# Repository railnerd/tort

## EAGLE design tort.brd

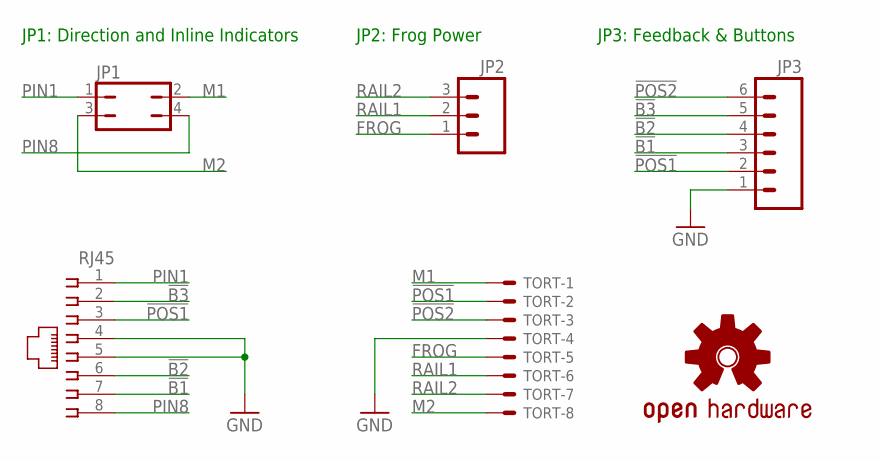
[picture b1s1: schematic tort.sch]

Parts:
JP1: JP2Q
JP2: M03-SCREW-5MM; SCREWTERMINAL-5MM-3
JP3: M063.5MM-6; SCREWTERMINAL-3.5MM-6
LOGO1: OSHW-LOGOL; OSHW-LOGO-L
RJ45: 215877-7
STANDOFF1: STAND-OFF
TORT: KK-156-8

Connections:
!B1: JP3.3, RJ45.7
!B2: JP3.4, RJ45.6
!B3: JP3.5, RJ45.2
!POS1: JP3.2, RJ45.3, TORT.2
!POS2: JP3.6, TORT.3
FROG: JP2.1, TORT.5
GND: JP3.1, RJ45.4, RJ45.5, TORT.4
M1: JP1.2, TORT.1
M2: JP1.3, TORT.8
PIN1: JP1.1, RJ45.1
PIN8: JP1.4, RJ45.8
RAIL1: JP2.2, TORT.6
RAIL2: JP2.3, TORT.7

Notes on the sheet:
JP1: Direction and Inline Indicators
JP2: Frog Power
JP3: Feedback & Buttons

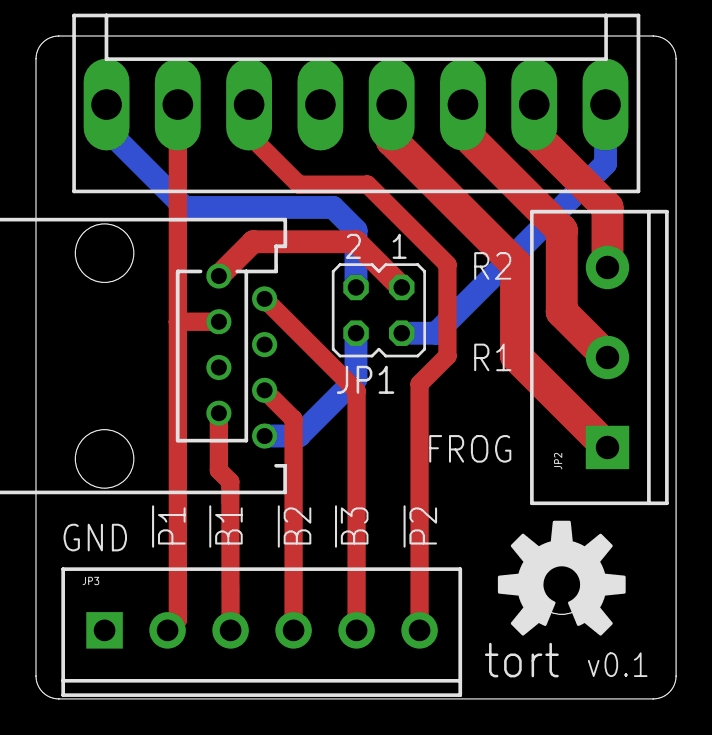
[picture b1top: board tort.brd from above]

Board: 2 copper layers, 35.6 x 36.8 mm, 7 parts (0 on the bottom side), 13 nets.

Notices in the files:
parts and their libraries:
SparkFun-Connectors: Licensing: CC v3.0 Share-Alike You are welcome to use this library for commercial purposes.
